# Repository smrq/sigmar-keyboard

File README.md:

# Sigmar Keyboard

40% split keyboard design

## PCB

The design for the PCB was done in KiCad. The PCB is designed according to the specifications of manufacturing with [JLCPCB](https://jlcpcb.com/).

## Firmware

Prerequisites:

* Podman
* dfu-programmer

Building:

* `make docker` to build the container image
* `make` to build the bootloader and firmware hex files

Flashing:

* `make flash left` or `make flash right`

### Building and flashing in WSL

* Install Ubuntu >= 22.04
* Install usbipd-win
* `sudo apt install dfu-programmer podman`

Flashing:

* In Powershell
	- `usbipd list`
		- Find the entry that corresponds with the keyboard (when in keyboard mode, VID/PID is f055:5164)
	- Press the reset button to switch to flashing mode
		- You will need another keyboard or the on-screen virtual keyboard from now on! If the latter, it might help to type the following commands beforehand, so you only need to press enter.
	- `usbipd wsl attach --busid=#-##`

* In WSL
	- `make flash-left` or `make flash-right`

### Flashing the bootloader with Arduino ISP

* Connect Arduino ISP
	* MOSI Pin 11 (programmer) -> B2 (target)
	* MISO Pin 12 -> B3
	* SCK Pin 13 -> B1
	* RST Pin 10 -> RST
* `make build/sigmar_[osx|windows]_bootloader.hex`
* `avrdude -p atmega32u4 -F -P COM4 -c stk500v1 -b 19200 -U flash:w:build/sigmar_[osx|windows]_bootloader.hex`
	* `-P COM4` should match the serial port for the Arduino ISP

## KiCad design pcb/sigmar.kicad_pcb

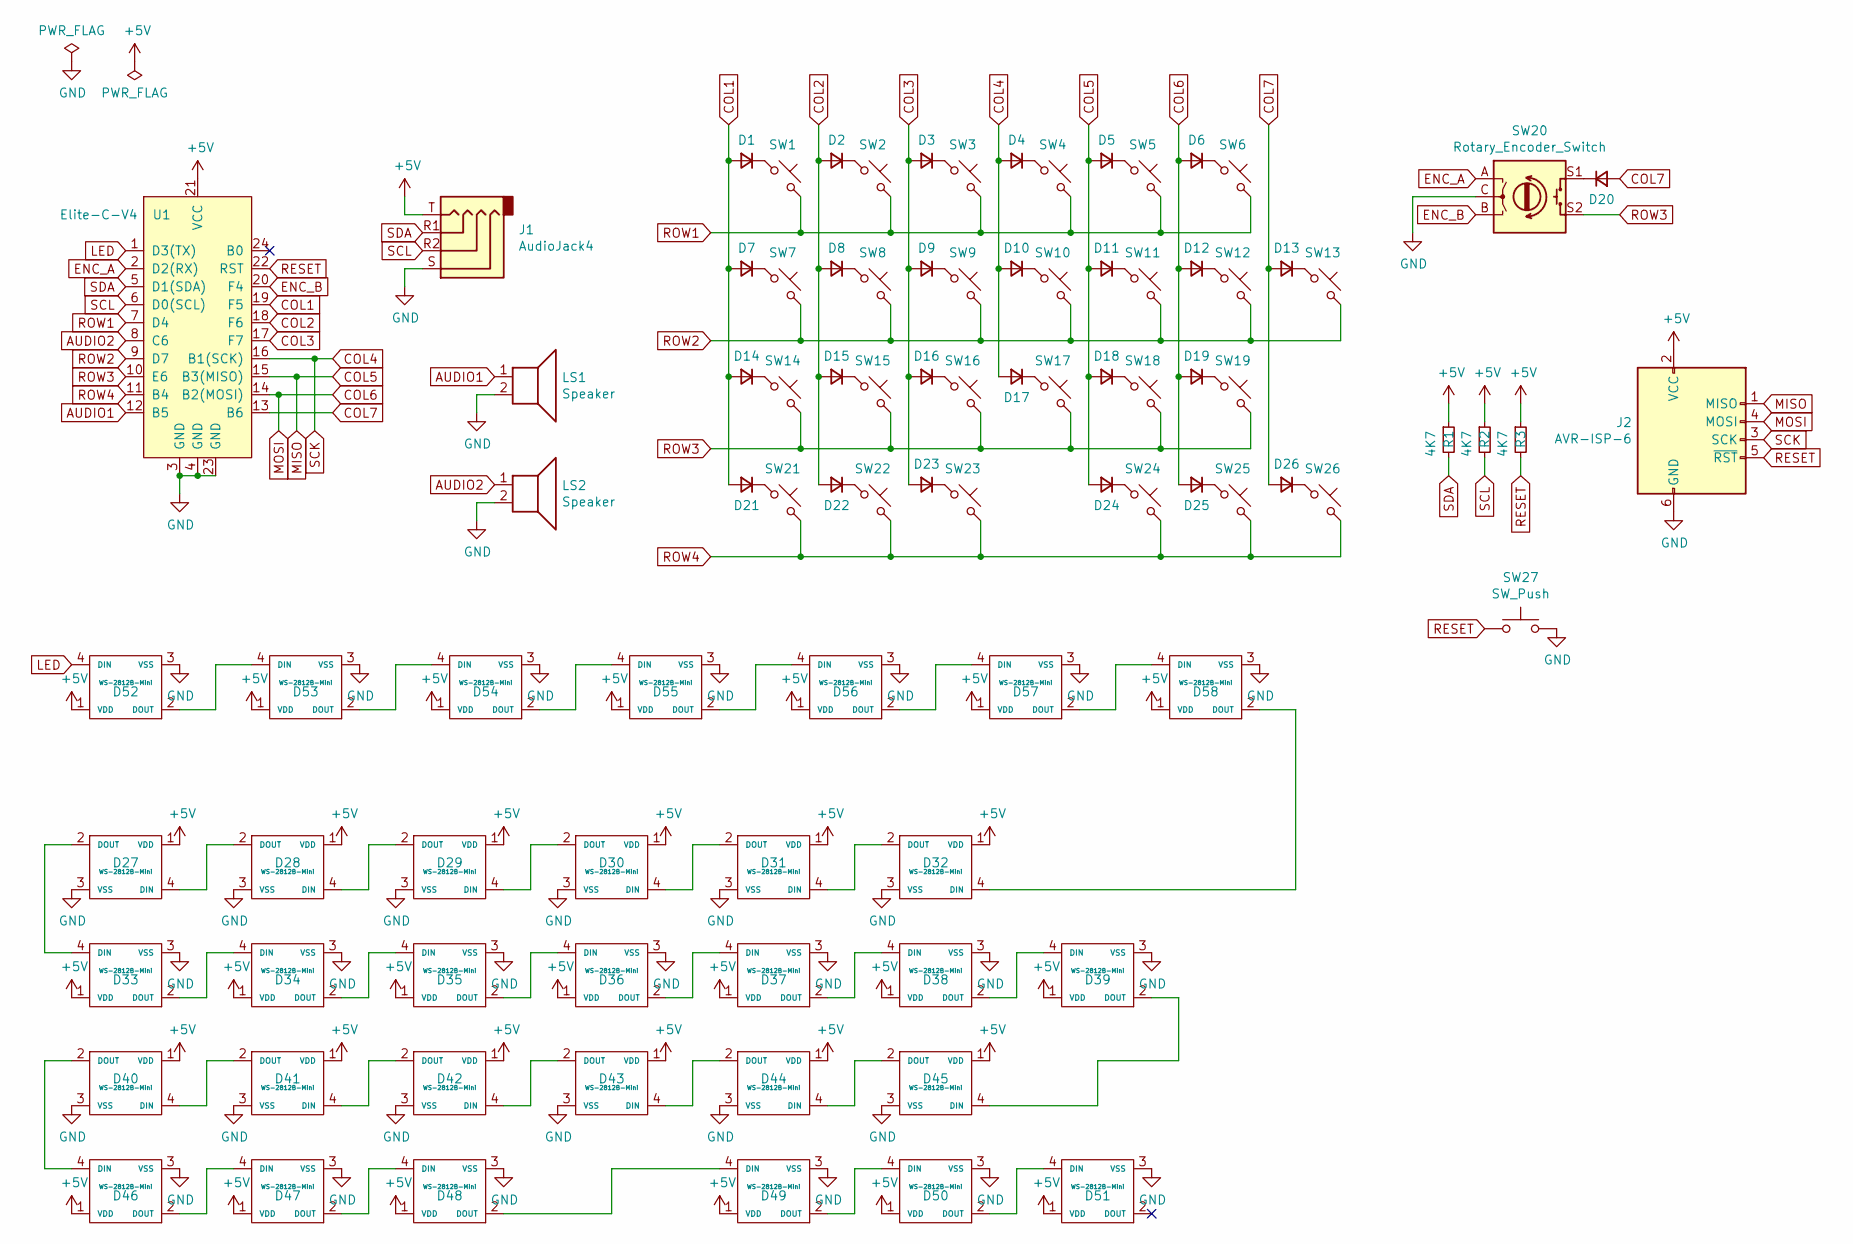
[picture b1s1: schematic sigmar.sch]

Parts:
D1, D2, D3, D4, D5, D6, D7, D8, D9, D10, D11, D12, D13, D14, D15, D16, D17, D18, D19, D20, D21, D22, D23, D24, D25, D26: D_Small; D_MiniMELF
D27, D28, D29, D30, D31, D32, D33, D34, D35, D36, D37, D38, D39, D40, D41, D42, D43, D44, D45, D46, D47, D48, D49, D50, D51: WS-2812B-Mini; LED_3535_Through_Reversible
D52, D53, D54, D55, D56, D57, D58: WS-2812B-Mini; LED_3535_Reversible
J1: AudioJack4; TRRS-PJ-320A_Reversible
J2: AVR-ISP-6; AVR-ISP
LS1, LS2: Speaker; KLJ-1102_Reversible
R1, R2, R3: 4K7; R_0805
SW1, SW2, SW3, SW4, SW5, SW6, SW7, SW8, SW9, SW10, SW11, SW12, SW14, SW15, SW16, SW17, SW18, SW19, SW21, SW22, SW23, SW24, SW25, SW26: SW_Push_45deg; Cherry_MX_1U_Reversible
SW13: SW_Push_45deg; Cherry_MX_2U_Vert_Reversible
SW20: Rotary_Encoder_Switch; RotaryEncoder_EC11_Reversible
SW27: SW_Push; SPST_MJTP1117_Reversible
U1: Elite-C-V4; Elite-C

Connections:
+5V: D27.1 (VDD), D28.1 (VDD), D29.1 (VDD), D30.1 (VDD), D31.1 (VDD), D32.1 (VDD), D33.1 (VDD), D34.1 (VDD), D35.1 (VDD), D36.1 (VDD), D37.1 (VDD), D38.1 (VDD), D39.1 (VDD), D40.1 (VDD), D41.1 (VDD), D42.1 (VDD), D43.1 (VDD), D44.1 (VDD), D45.1 (VDD), D46.1 (VDD), D47.1 (VDD), D48.1 (VDD), D49.1 (VDD), D50.1 (VDD), D51.1 (VDD), D52.1 (VDD), D53.1 (VDD), D54.1 (VDD), D55.1 (VDD), D56.1 (VDD), D57.1 (VDD), D58.1 (VDD), J1.T, J2.2 (VCC), R1.1, R2.1, R3.1, U1.21 (VCC)
AUDIO1: LS1.1, U1.12 (B5)
AUDIO2: LS2.1, U1.8 (C6)
COL1: D1.2 (A), D7.2 (A), D14.2 (A), D21.2 (A), U1.19 (F5)
COL2: D2.2 (A), D8.2 (A), D15.2 (A), D22.2 (A), U1.18 (F6)
COL3: D3.2 (A), D9.2 (A), D16.2 (A), D23.2 (A), U1.17 (F7)
COL4: D4.2 (A), D10.2 (A), D17.2 (A), J2.3 (SCK), U1.16 (B1(SCK))
COL5: D5.2 (A), D11.2 (A), D18.2 (A), D24.2 (A), J2.1 (MISO), U1.15 (B3(MISO))
COL6: D6.2 (A), D12.2 (A), D19.2 (A), D25.2 (A), J2.4 (MOSI), U1.14 (B2(MOSI))
COL7: D13.2 (A), D20.2 (A), D26.2 (A), U1.13 (B6)
ENC_A: SW20.A, U1.2 (D2(RX))
ENC_B: SW20.B, U1.20 (F4)
GND: D27.3 (VSS), D28.3 (VSS), D29.3 (VSS), D30.3 (VSS), D31.3 (VSS), D32.3 (VSS), D33.3 (VSS), D34.3 (VSS), D35.3 (VSS), D36.3 (VSS), D37.3 (VSS), D38.3 (VSS), D39.3 (VSS), D40.3 (VSS), D41.3 (VSS), D42.3 (VSS), D43.3 (VSS), D44.3 (VSS), D45.3 (VSS), D46.3 (VSS), D47.3 (VSS), D48.3 (VSS), D49.3 (VSS), D50.3 (VSS), D51.3 (VSS), D52.3 (VSS), D53.3 (VSS), D54.3 (VSS), D55.3 (VSS), D56.3 (VSS), D57.3 (VSS), D58.3 (VSS), J1.S, J2.6 (GND), LS1.2, LS2.2, SW20.C, SW27.2, U1.3 (GND), U1.4 (GND), U1.23 (GND)
LED: D52.4 (DIN), U1.1 (D3(TX))
unnamed: D1.1 (K), SW1.1
unnamed: D2.1 (K), SW2.1
unnamed: D3.1 (K), SW3.1
unnamed: D4.1 (K), SW4.1
unnamed: D5.1 (K), SW5.1
unnamed: D6.1 (K), SW6.1
unnamed: D7.1 (K), SW7.1
unnamed: D8.1 (K), SW8.1
unnamed: D9.1 (K), SW9.1
unnamed: D10.1 (K), SW10.1
unnamed: D11.1 (K), SW11.1
unnamed: D12.1 (K), SW12.1
unnamed: D13.1 (K), SW13.1
unnamed: D14.1 (K), SW14.1
unnamed: D15.1 (K), SW15.1
unnamed: D16.1 (K), SW16.1
unnamed: D17.1 (K), SW17.1
unnamed: D18.1 (K), SW18.1
unnamed: D19.1 (K), SW19.1
unnamed: D20.1 (K), SW20.S1
unnamed: D21.1 (K), SW21.1
unnamed: D22.1 (K), SW22.1
unnamed: D23.1 (K), SW23.1
unnamed: D24.1 (K), SW24.1
unnamed: D25.1 (K), SW25.1
unnamed: D26.1 (K), SW26.1
unnamed: D27.2 (DOUT), D33.4 (DIN)
unnamed: D27.4 (DIN), D28.2 (DOUT)
unnamed: D28.4 (DIN), D29.2 (DOUT)
unnamed: D29.4 (DIN), D30.2 (DOUT)
unnamed: D30.4 (DIN), D31.2 (DOUT)
unnamed: D31.4 (DIN), D32.2 (DOUT)
unnamed: D32.4 (DIN), D58.2 (DOUT)
unnamed: D33.2 (DOUT), D34.4 (DIN)
unnamed: D34.2 (DOUT), D35.4 (DIN)
unnamed: D35.2 (DOUT), D36.4 (DIN)
unnamed: D36.2 (DOUT), D37.4 (DIN)
unnamed: D37.2 (DOUT), D38.4 (DIN)
unnamed: D38.2 (DOUT), D39.4 (DIN)
unnamed: D39.2 (DOUT), D45.4 (DIN)
unnamed: D40.2 (DOUT), D46.4 (DIN)
unnamed: D40.4 (DIN), D41.2 (DOUT)
unnamed: D41.4 (DIN), D42.2 (DOUT)
unnamed: D42.4 (DIN), D43.2 (DOUT)
unnamed: D43.4 (DIN), D44.2 (DOUT)
unnamed: D44.4 (DIN), D45.2 (DOUT)
unnamed: D46.2 (DOUT), D47.4 (DIN)
unnamed: D47.2 (DOUT), D48.4 (DIN)
unnamed: D48.2 (DOUT), D49.4 (DIN)
unnamed: D49.2 (DOUT), D50.4 (DIN)
unnamed: D50.2 (DOUT), D51.4 (DIN)
unnamed: D52.2 (DOUT), D53.4 (DIN)
unnamed: D53.2 (DOUT), D54.4 (DIN)
unnamed: D54.2 (DOUT), D55.4 (DIN)
unnamed: D55.2 (DOUT), D56.4 (DIN)
unnamed: D56.2 (DOUT), D57.4 (DIN)
unnamed: D57.2 (DOUT), D58.4 (DIN)
RESET: J2.5 (~RST), R3.2, SW27.1, U1.22 (RST)
ROW1: SW1.2, SW2.2, SW3.2, SW4.2, SW5.2, SW6.2, U1.7 (D4)
ROW2: SW7.2, SW8.2, SW9.2, SW10.2, SW11.2, SW12.2, SW13.2, U1.9 (D7)
ROW3: SW14.2, SW15.2, SW16.2, SW17.2, SW18.2, SW19.2, SW20.S2, U1.10 (E6)
ROW4: SW21.2, SW22.2, SW23.2, SW24.2, SW25.2, SW26.2, U1.11 (B4)
SCL: J1.R2, R2.2, U1.6 (D0(SCL))
SDA: J1.R1, R1.2, U1.5 (D1(SDA))

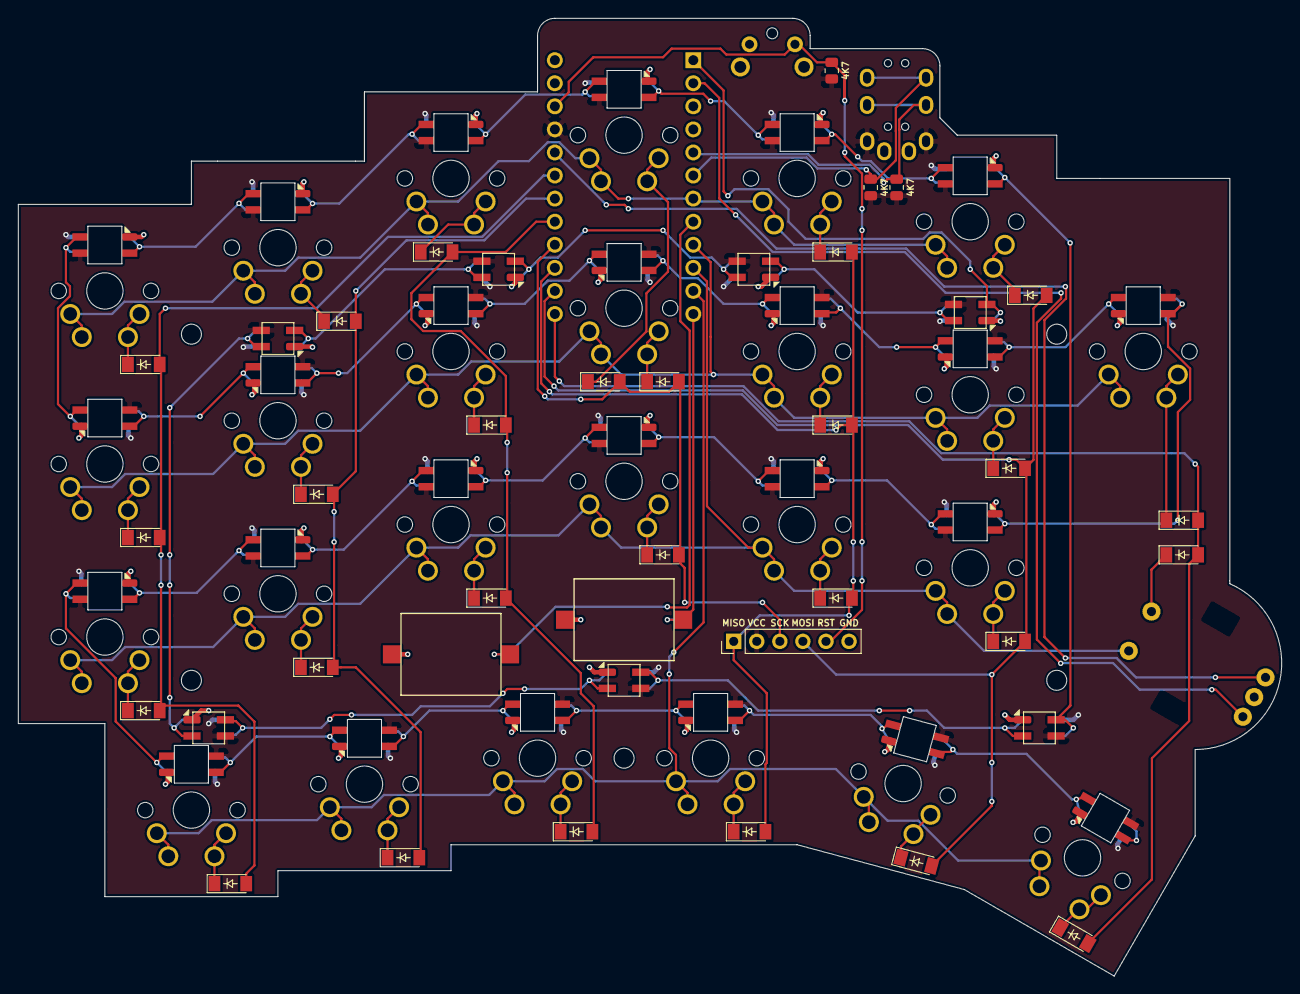
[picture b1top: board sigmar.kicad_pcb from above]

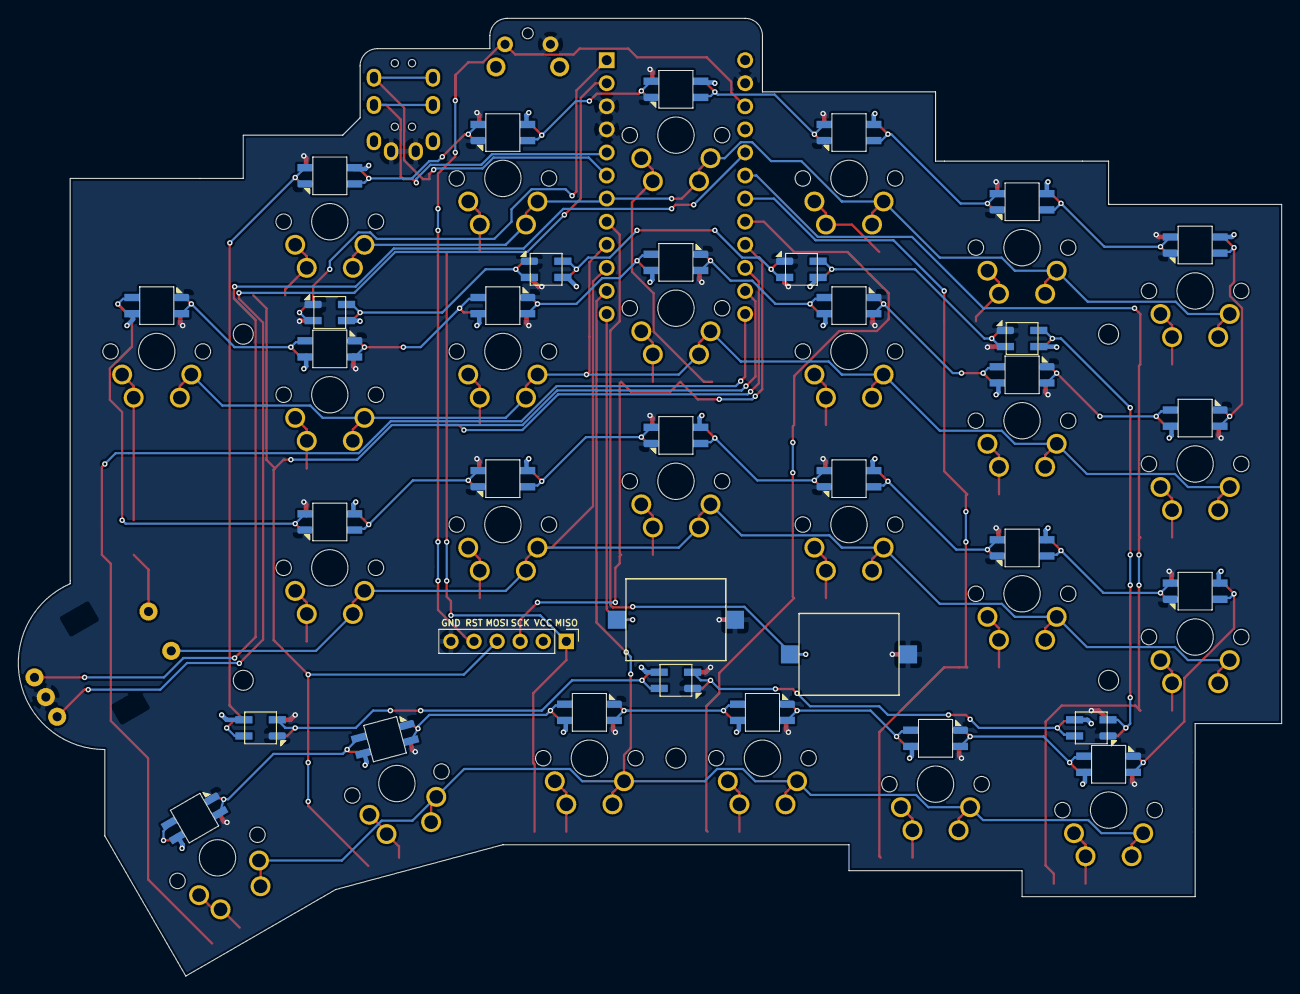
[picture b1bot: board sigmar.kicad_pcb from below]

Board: 2 copper layers, 139.1 x 105.4 mm, 93 parts (37 on the bottom side), 78 nets.

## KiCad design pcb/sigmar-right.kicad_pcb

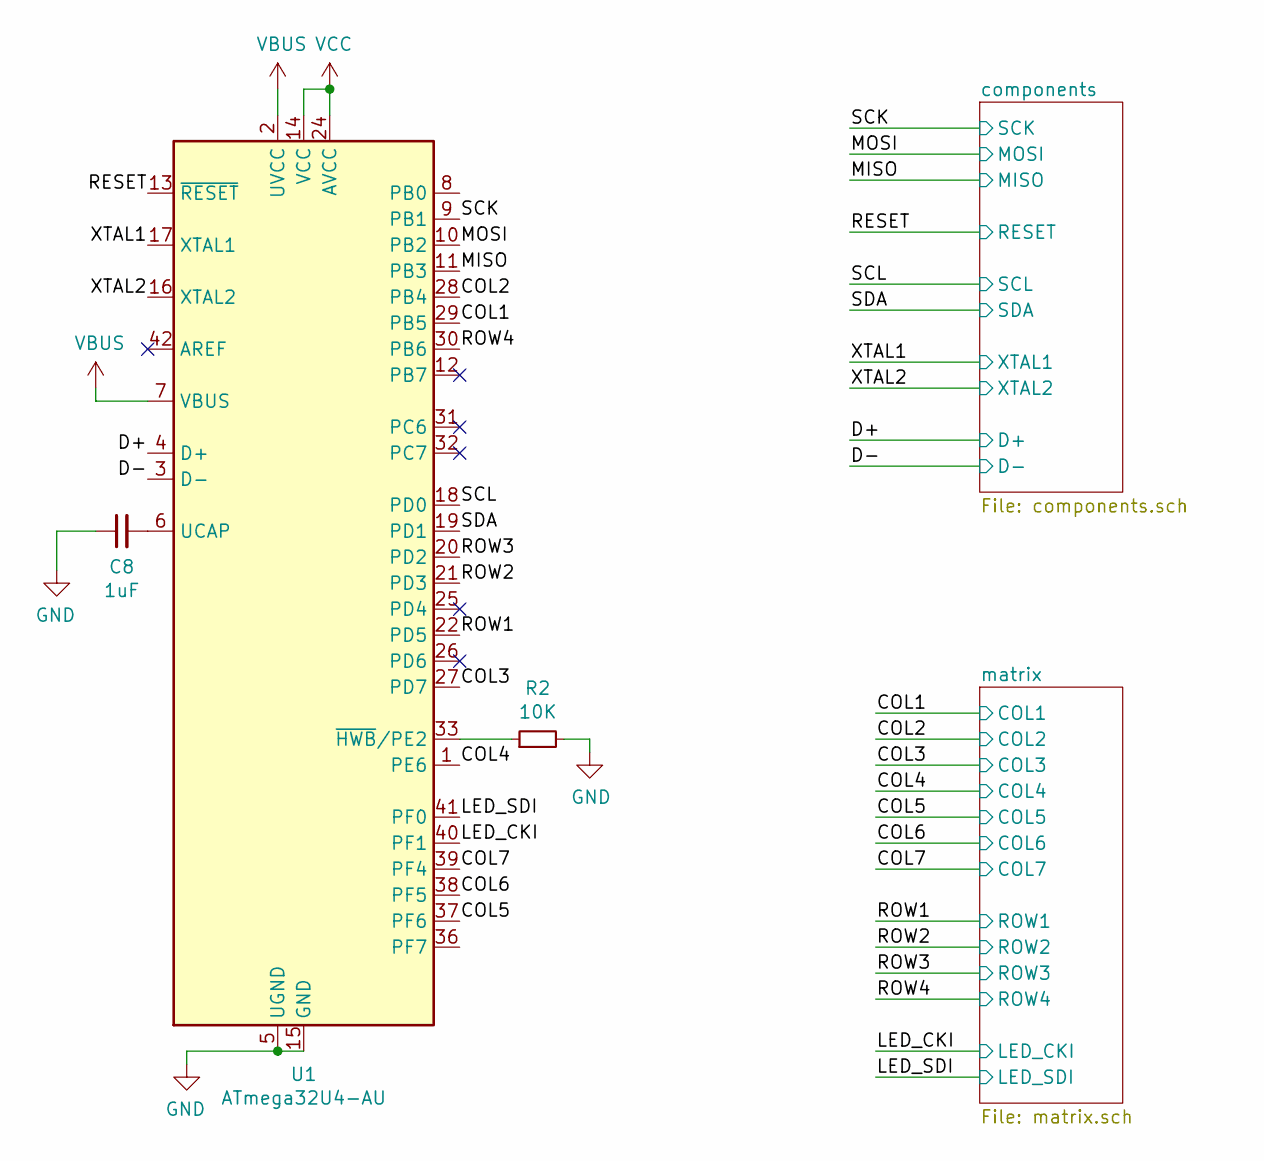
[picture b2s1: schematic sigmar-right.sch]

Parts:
C8: 1uF; C_0805_2012Metric
R2: 10K; R_0805_2012Metric
U1: ATmega32U4-AU; TQFP-44_10x10mm_P0.8mm

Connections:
/COL1: U1.29 (PB5); also elsewhere on the board
/COL2: U1.28 (PB4); also elsewhere on the board
/COL3: U1.27 (PD7); also elsewhere on the board
/COL4: U1.1 (PE6); also elsewhere on the board
/COL5: U1.37 (PF6); also elsewhere on the board
/COL6: U1.38 (PF5); also elsewhere on the board
/COL7: U1.39 (PF4); also elsewhere on the board
/D+: U1.4 (D+); also elsewhere on the board
/D-: U1.3 (D-); also elsewhere on the board
/LED_CKI: U1.40 (PF1); also elsewhere on the board
/LED_SDI: U1.41 (PF0); also elsewhere on the board
/MISO: U1.11 (PB3); also elsewhere on the board
/MOSI: U1.10 (PB2); also elsewhere on the board
/RESET: U1.13 (~RESET); also elsewhere on the board
/ROW1: U1.22 (PD5); also elsewhere on the board
/ROW2: U1.21 (PD3); also elsewhere on the board
/ROW3: U1.20 (PD2); also elsewhere on the board
/ROW4: U1.30 (PB6); also elsewhere on the board
/SCK: U1.9 (PB1); also elsewhere on the board
/SCL: U1.18 (PD0); also elsewhere on the board
/SDA: U1.19 (PD1); also elsewhere on the board
/XTAL1: U1.17 (XTAL1); also elsewhere on the board
/XTAL2: U1.16 (XTAL2); also elsewhere on the board
GND: C8.1, R2.2, U1.5 (UGND), U1.15 (GND), U1.23 (GND), U1.35 (GND), U1.43 (GND); also elsewhere on the board
unnamed: C8.2, U1.6 (UCAP)
unnamed: R2.1, U1.33 (~HWB~/PE2)
VBUS: U1.2 (UVCC), U1.7 (VBUS); also elsewhere on the board
VCC: U1.14 (VCC), U1.24 (AVCC), U1.34 (VCC), U1.44 (AVCC); also elsewhere on the board

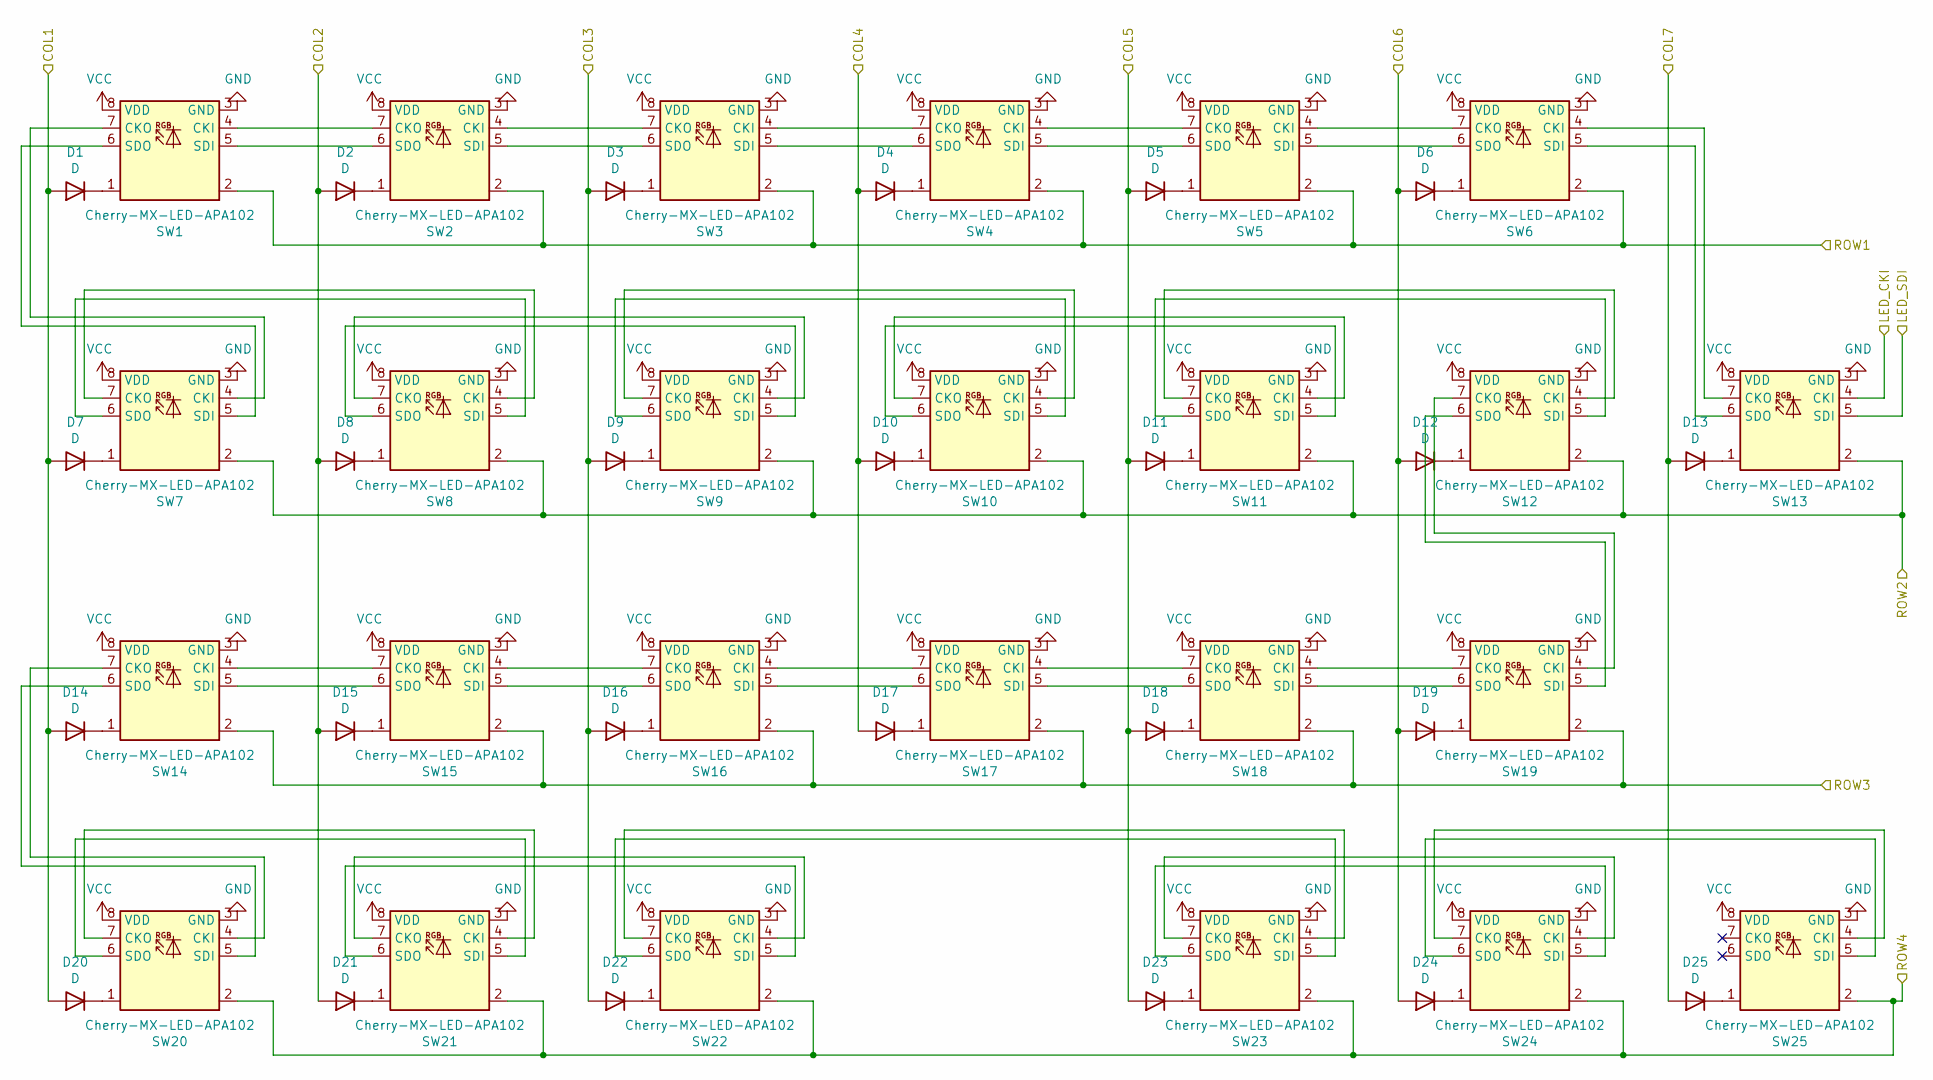
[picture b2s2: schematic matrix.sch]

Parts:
D1, D2, D3, D4, D5, D6, D7, D8, D9, D10, D11, D12, D13, D14, D15, D16, D17, D18, D19, D20, D21, D22, D23, D24, D25: D; D_MiniMELF
SW1, SW2, SW3, SW4, SW5, SW6, SW14, SW15, SW16, SW17, SW18, SW19: Cherry-MX-LED-APA102; SW_Cherry_MX_RGB_R2L
SW7, SW8, SW9, SW10, SW11, SW12, SW20, SW21, SW22, SW23, SW24, SW25: Cherry-MX-LED-APA102; SW_Cherry_MX_RGB_L2R
SW13: Cherry-MX-LED-APA102; SW_Cherry_MX_RGB_R2L_2U

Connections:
/COL1: D1.2 (A), D7.2 (A), D14.2 (A), D20.2 (A); also elsewhere on the board
/COL2: D2.2 (A), D8.2 (A), D15.2 (A), D21.2 (A); also elsewhere on the board
/COL3: D3.2 (A), D9.2 (A), D16.2 (A), D22.2 (A); also elsewhere on the board
/COL4: D4.2 (A), D10.2 (A), D17.2 (A); also elsewhere on the board
/COL5: D5.2 (A), D11.2 (A), D18.2 (A), D23.2 (A); also elsewhere on the board
/COL6: D6.2 (A), D12.2 (A), D19.2 (A), D24.2 (A); also elsewhere on the board
/COL7: D13.2 (A), D25.2 (A); also elsewhere on the board
/LED_CKI: SW13.4 (CKI); also elsewhere on the board
/LED_SDI: SW13.5 (SDI); also elsewhere on the board
/ROW1: SW1.2, SW2.2, SW3.2, SW4.2, SW5.2, SW6.2; also elsewhere on the board
/ROW2: SW7.2, SW8.2, SW9.2, SW10.2, SW11.2, SW12.2, SW13.2; also elsewhere on the board
/ROW3: SW14.2, SW15.2, SW16.2, SW17.2, SW18.2, SW19.2; also elsewhere on the board
/ROW4: SW20.2, SW21.2, SW22.2, SW23.2, SW24.2, SW25.2; also elsewhere on the board
GND: SW1.3 (GND), SW2.3 (GND), SW3.3 (GND), SW4.3 (GND), SW5.3 (GND), SW6.3 (GND), SW7.3 (GND), SW8.3 (GND), SW9.3 (GND), SW10.3 (GND), SW11.3 (GND), SW12.3 (GND), SW13.3 (GND), SW14.3 (GND), SW15.3 (GND), SW16.3 (GND), SW17.3 (GND), SW18.3 (GND), SW19.3 (GND), SW20.3 (GND), SW21.3 (GND), SW22.3 (GND), SW23.3 (GND), SW24.3 (GND), SW25.3 (GND); also elsewhere on the board
unnamed: D1.1 (K), SW1.1
unnamed: D2.1 (K), SW2.1
unnamed: D3.1 (K), SW3.1
unnamed: D4.1 (K), SW4.1
unnamed: D5.1 (K), SW5.1
unnamed: D6.1 (K), SW6.1
unnamed: D7.1 (K), SW7.1
unnamed: D8.1 (K), SW8.1
unnamed: D9.1 (K), SW9.1
unnamed: D10.1 (K), SW10.1
unnamed: D11.1 (K), SW11.1
unnamed: D12.1 (K), SW12.1
unnamed: D13.1 (K), SW13.1
unnamed: D14.1 (K), SW14.1
unnamed: D15.1 (K), SW15.1
unnamed: D16.1 (K), SW16.1
unnamed: D17.1 (K), SW17.1
unnamed: D18.1 (K), SW18.1
unnamed: D19.1 (K), SW19.1
unnamed: D20.1 (K), SW20.1
unnamed: D21.1 (K), SW21.1
unnamed: D22.1 (K), SW22.1
unnamed: D23.1 (K), SW23.1
unnamed: D24.1 (K), SW24.1
unnamed: D25.1 (K), SW25.1
unnamed: SW1.4 (CKI), SW2.7 (CKO)
unnamed: SW1.5 (SDI), SW2.6 (SDO)
unnamed: SW1.6 (SDO), SW7.5 (SDI)
unnamed: SW1.7 (CKO), SW7.4 (CKI)
unnamed: SW2.4 (CKI), SW3.7 (CKO)
unnamed: SW2.5 (SDI), SW3.6 (SDO)
unnamed: SW3.4 (CKI), SW4.7 (CKO)
unnamed: SW3.5 (SDI), SW4.6 (SDO)
unnamed: SW4.4 (CKI), SW5.7 (CKO)
unnamed: SW4.5 (SDI), SW5.6 (SDO)
unnamed: SW5.4 (CKI), SW6.7 (CKO)
unnamed: SW5.5 (SDI), SW6.6 (SDO)
unnamed: SW7.6 (SDO), SW8.5 (SDI)
unnamed: SW7.7 (CKO), SW8.4 (CKI)
unnamed: SW8.6 (SDO), SW9.5 (SDI)
unnamed: SW8.7 (CKO), SW9.4 (CKI)
unnamed: SW9.7 (CKO), SW10.4 (CKI)
unnamed: SW9.6 (SDO), SW10.5 (SDI)
unnamed: SW10.6 (SDO), SW11.5 (SDI)
unnamed: SW10.7 (CKO), SW11.4 (CKI)
unnamed: SW11.6 (SDO), SW12.5 (SDI)
unnamed: SW11.7 (CKO), SW12.4 (CKI)
unnamed: SW12.6 (SDO), SW19.5 (SDI)
unnamed: SW12.7 (CKO), SW19.4 (CKI)
unnamed: SW6.5 (SDI), SW13.6 (SDO)
unnamed: SW6.4 (CKI), SW13.7 (CKO)
unnamed: SW14.4 (CKI), SW15.7 (CKO)
unnamed: SW14.5 (SDI), SW15.6 (SDO)
unnamed: SW14.6 (SDO), SW20.5 (SDI)
unnamed: SW14.7 (CKO), SW20.4 (CKI)
unnamed: SW15.4 (CKI), SW16.7 (CKO)
unnamed: SW15.5 (SDI), SW16.6 (SDO)
unnamed: SW16.4 (CKI), SW17.7 (CKO)
unnamed: SW16.5 (SDI), SW17.6 (SDO)
unnamed: SW17.4 (CKI), SW18.7 (CKO)
unnamed: SW17.5 (SDI), SW18.6 (SDO)
unnamed: SW18.4 (CKI), SW19.7 (CKO)
unnamed: SW18.5 (SDI), SW19.6 (SDO)
unnamed: SW20.6 (SDO), SW21.5 (SDI)
unnamed: SW20.7 (CKO), SW21.4 (CKI)
unnamed: SW21.6 (SDO), SW22.5 (SDI)
unnamed: SW21.7 (CKO), SW22.4 (CKI)
unnamed: SW22.6 (SDO), SW23.5 (SDI)
unnamed: SW22.7 (CKO), SW23.4 (CKI)
unnamed: SW23.6 (SDO), SW24.5 (SDI)
unnamed: SW23.7 (CKO), SW24.4 (CKI)
unnamed: SW24.6 (SDO), SW25.5 (SDI)
unnamed: SW24.7 (CKO), SW25.4 (CKI)
VCC: SW1.8 (VDD), SW2.8 (VDD), SW3.8 (VDD), SW4.8 (VDD), SW5.8 (VDD), SW6.8 (VDD), SW7.8 (VDD), SW8.8 (VDD), SW9.8 (VDD), SW10.8 (VDD), SW11.8 (VDD), SW12.8 (VDD), SW13.8 (VDD), SW14.8 (VDD), SW15.8 (VDD), SW16.8 (VDD), SW17.8 (VDD), SW18.8 (VDD), SW19.8 (VDD), SW20.8 (VDD), SW21.8 (VDD), SW22.8 (VDD), SW23.8 (VDD), SW24.8 (VDD), SW25.8 (VDD); also elsewhere on the board

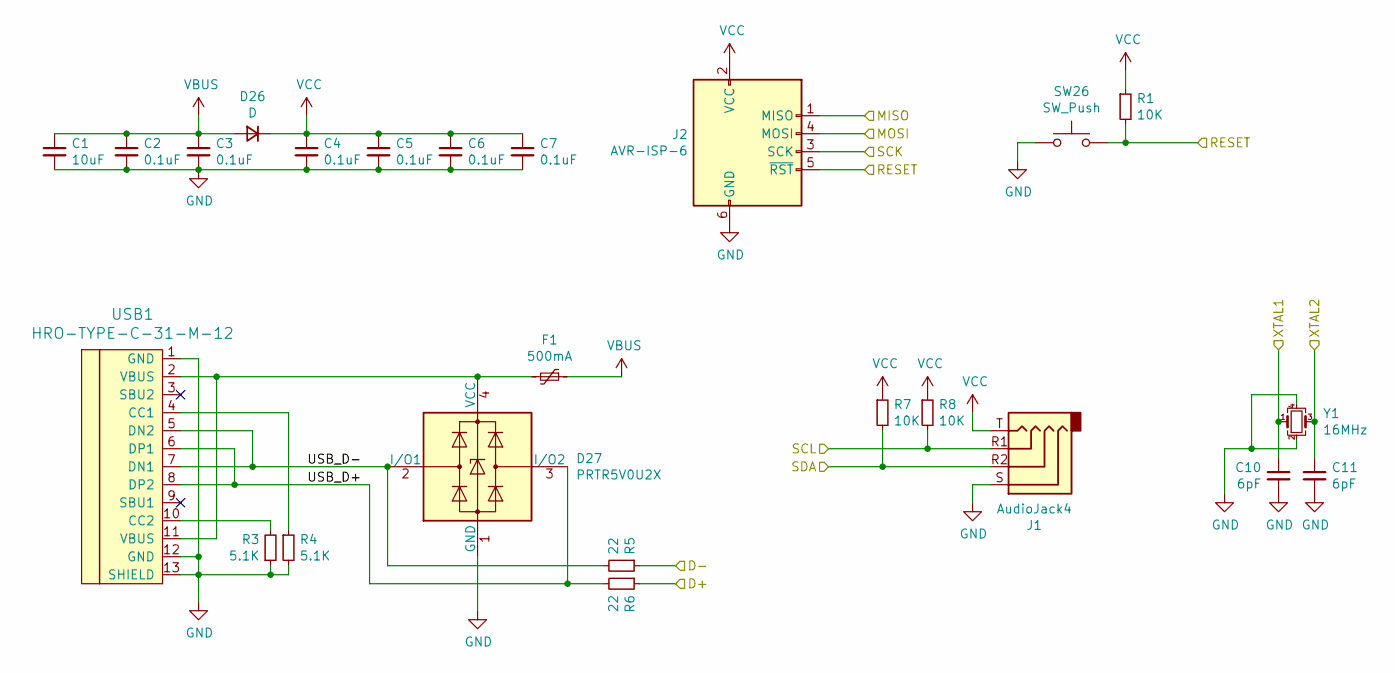
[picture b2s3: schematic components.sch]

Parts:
C1: 10uF; C_0805_2012Metric
C2, C3, C4, C5, C6, C7: 0.1uF; C_0805_2012Metric
C10, C11: 6pF; C_0805_2012Metric
D26: D; D_MiniMELF
D27: PRTR5V0U2X; SOT-143
F1: 500mA; Fuse_0805_2012Metric
J1: AudioJack4; TRRS-PJ-320A
J2: AVR-ISP-6
R1, R7, R8: 10K; R_0805_2012Metric
R3, R4: 5.1K; R_0805_2012Metric
R5, R6: 22; R_0805_2012Metric
SW26: SW_Push; LL3301NF065QG
USB1: HRO-TYPE-C-31-M-12
Y1: 16MHz; Crystal_SMD_3225-4Pin_3.2x2.5mm

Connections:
/D+: R6.1; also elsewhere on the board
/D-: R5.1; also elsewhere on the board
/MISO: J2.1 (MISO); also elsewhere on the board
/MOSI: J2.4 (MOSI); also elsewhere on the board
/RESET: J2.5 (~RST), R1.2, SW26.2; also elsewhere on the board
/SCK: J2.3 (SCK); also elsewhere on the board
/SCL: J1.R1, R8.2; also elsewhere on the board
/SDA: J1.R2, R7.2; also elsewhere on the board
/XTAL1: C10.1, Y1.1; also elsewhere on the board
/XTAL2: C11.1, Y1.3; also elsewhere on the board
/components/USB_D+: D27.3 (I/O2), R6.2, USB1.6 (DP1), USB1.8 (DP2)
/components/USB_D-: D27.2 (I/O1), R5.2, USB1.5 (DN2), USB1.7 (DN1)
GND: C1.2, C2.2, C3.2, C4.2, C5.2, C6.2, C7.2, C10.2, C11.2, D27.1 (GND), J1.S, J2.6 (GND), R3.1, R4.2, SW26.1, USB1.1 (GND), USB1.12 (GND), USB1.13 (SHIELD), Y1.2, Y1.4; also elsewhere on the board
unnamed: D27.4 (VCC), F1.2, USB1.2 (VBUS), USB1.11 (VBUS)
unnamed: R3.2, USB1.10 (CC2)
unnamed: R4.1, USB1.4 (CC1)
VBUS: C1.1, C2.1, C3.1, D26.2 (A), F1.1; also elsewhere on the board
VCC: C4.1, C5.1, C6.1, C7.1, D26.1 (K), J1.T, J2.2 (VCC), R1.1, R7.1, R8.1; also elsewhere on the board

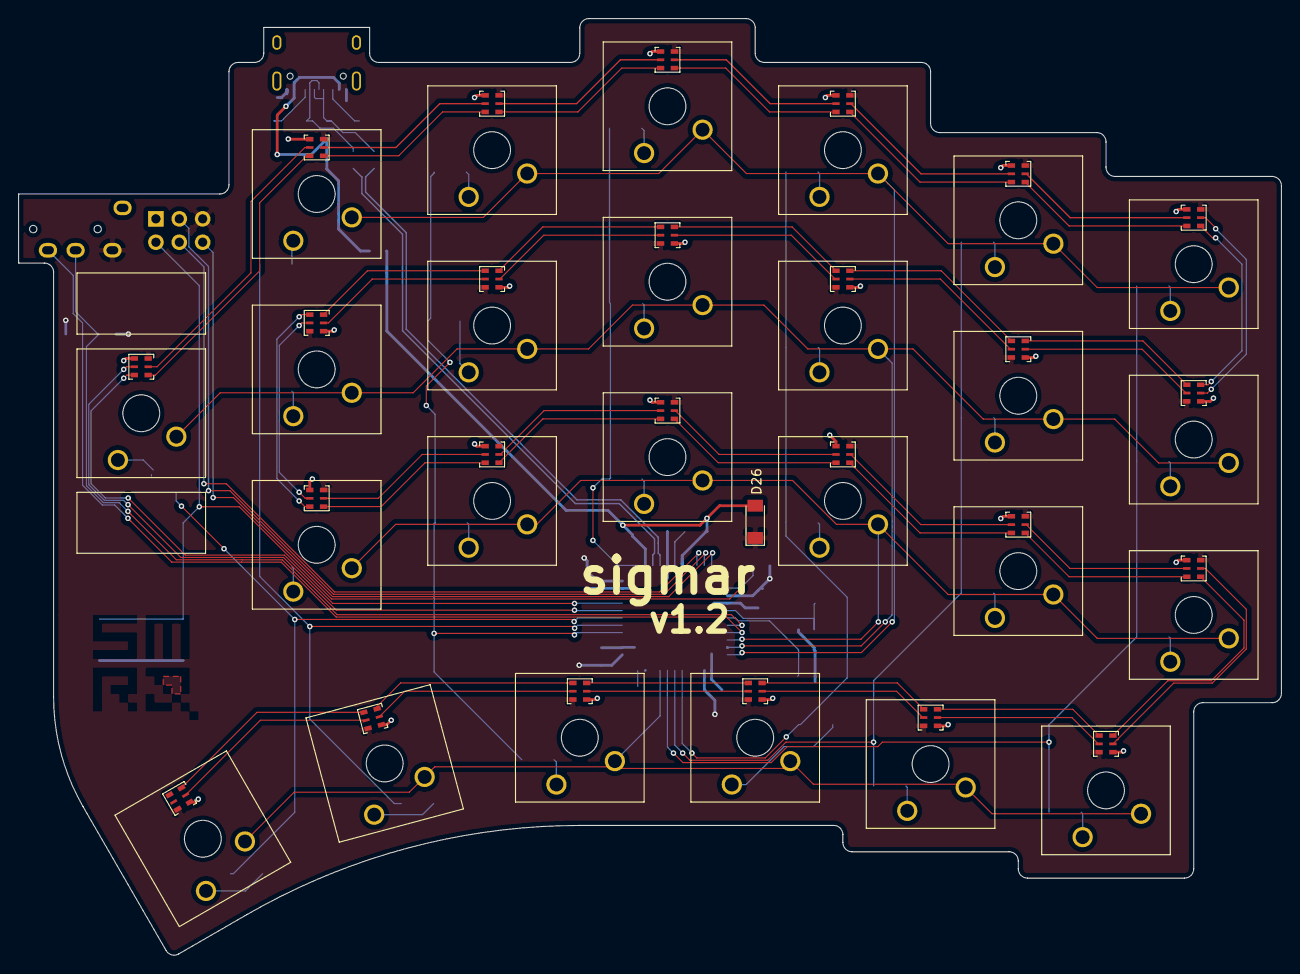
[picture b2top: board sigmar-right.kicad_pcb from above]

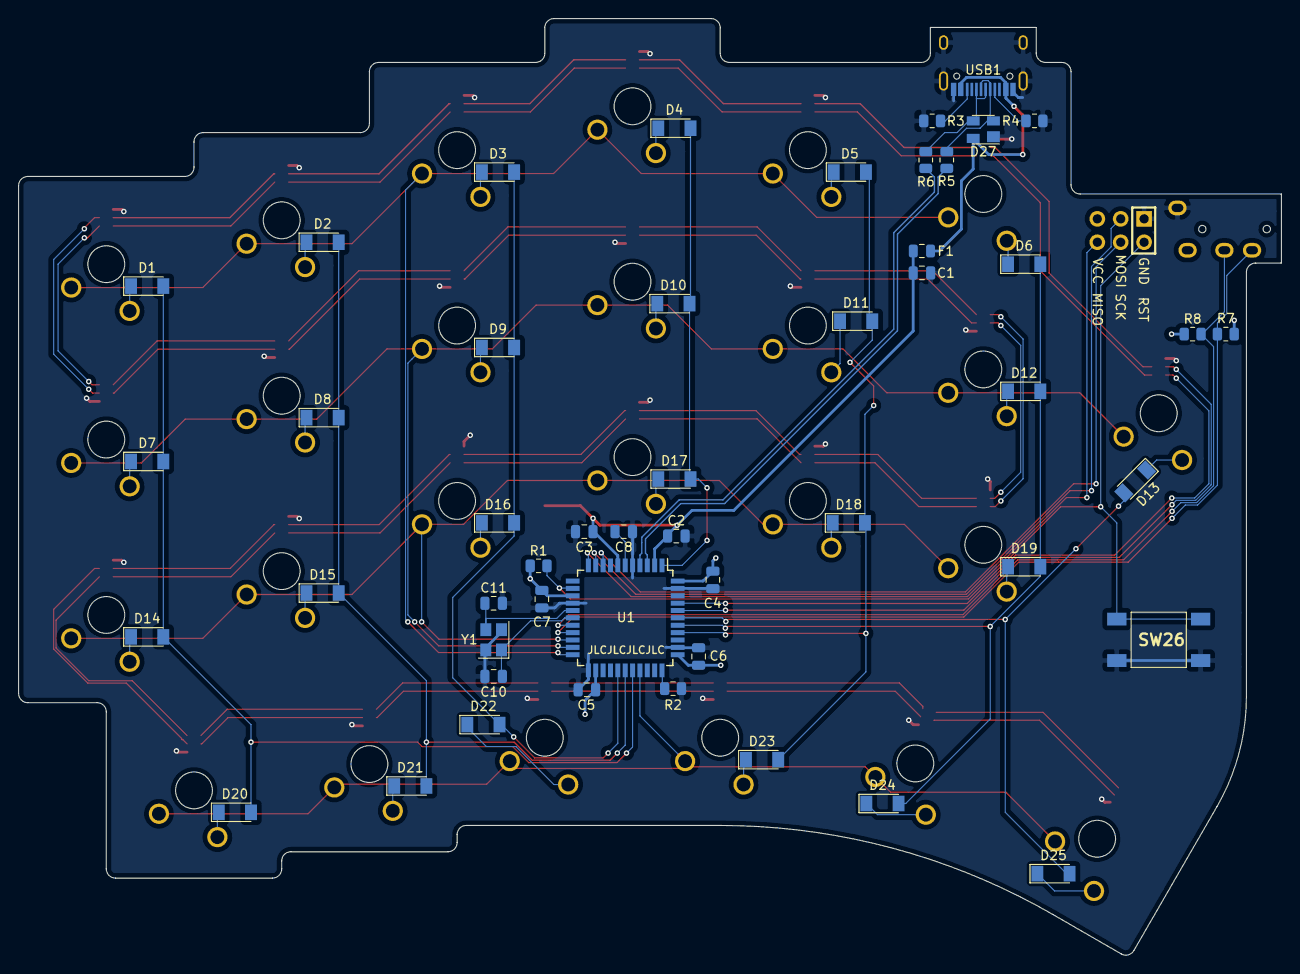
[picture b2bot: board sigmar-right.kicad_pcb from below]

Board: 2 copper layers, 137.2 x 101.7 mm, 77 parts (51 on the bottom side), 106 nets.

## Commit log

2021-05-14 Initial keyplate design
2021-05-14 Tweak keyplate design
2021-05-15 QMK firmware
2021-05-20 Update keymap
2021-05-23 pcb wip
2021-05-23 Squashed 'pcb/Type-C.pretty/' content from commit fecd1a97d
    git-subtree-dir: pcb/Type-C.pretty
    git-subtree-split: fecd1a97dee885e7daf32da80dfa47e726d59529
2021-05-23 pcb design nearly finalized
2021-05-23 pcb updates
2021-05-23 pcb left v1.2
2021-05-24 3d models
2021-05-24 fine tuning traces
2021-05-24 adjust
2021-05-24 pcb fixes
2021-05-24 rename schematic and pcb
2021-05-25 right hand pcb
2021-05-25 pcb v1.2 final
2021-05-25 make room for stabilizers
2021-05-27 Squashed 'pcb/Keebio-Parts.pretty/' content from commit c7ae3b446
    git-subtree-dir: pcb/Keebio-Parts.pretty
    git-subtree-split: c7ae3b44674679f4d767767c002fed1eacd414a1
2021-06-02 case design
2021-06-02 pcb v1.3
2021-06-03 pcb v1.3 final
2021-06-07 case updates
2021-06-10 case v1.3 final
2021-06-10 case v1.3 svg
2021-06-30 Firmware updates
2021-07-01 Keymap updates
2021-07-13 Fix screw holes in keyplate
2021-07-13 Tweak keymap
2021-07-27 Increase screw hole size for back plate
2021-08-12 Keymap updates for win vs osx
2022-10-04 Update keymap and fix build
